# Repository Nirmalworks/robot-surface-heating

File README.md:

# Robotic Surface Heating

A ROS 2 system for autonomous, closed-loop thermal conditioning of a surface. A
Universal Robots UR10e holds a hot-air tool while an array of FLIR thermal
cameras reconstructs a live 3D temperature field. A planning layer continuously
identifies the coldest region of the target surface and directs the arm to heat
it, repeating until the surface reaches a uniform temperature.

---

## Table of contents

1. [Overview](#1-overview)
2. [What this project achieves](#2-what-this-project-achieves)
3. [ROS 2 concepts used here](#3-ros-2-concepts-used-here)
4. [System architecture](#4-system-architecture)
5. [Runtime pipeline](#5-runtime-pipeline)
6. [Controllers compared: Greedy vs. MPC](#6-controllers-compared-greedy-vs-mpc)
7. [Project structure](#project-structure)
8. [Source files by package (detailed reference)](#7-source-files-by-package-detailed-reference)
9. [Configuration](#8-configuration)
10. [Starting a new "move-only" project](#9-starting-a-new-move-only-project)
11. [Driving the arm from a custom model](#10-driving-the-arm-from-a-custom-model)
12. [Quick start  running the heating demo](#11-quick-start--running-the-heating-demo)
13. [Full research paper](#12-research-paper)
14. [TRIAC intensity stage: circuit files](#13-triac-intensity-stage-circuit-files)
15. [Experiment photos and videos](#14-experiment-photos-and-videos)

---

## 1. Overview

The system runs a single control loop. Thermal cameras observe the surface, the
perception layer locates the coldest region, the planner converts that region
into a target pose, and the arm moves there and applies heat. As each cold spot
warms, a new coldest region appears, and the loop continues until the surface is
evenly heated.

---

## 2. What this project achieves

This work automates a process that is normally manual: bringing a surface to a
uniform target temperature with a robot-mounted heat gun. The contribution is
that **both the trajectory and the heating intensity are controlled together** —
prior automated approaches move the tool but leave intensity fixed.

**System built**

- A **TRIAC-based intensity stage** (custom PCB) that modulates the 1500 W heat
  gun via phase-angle firing, giving continuous, repeatable control of delivered
  power. Open-loop characterization is monotonic and repeatable across the firing
  range.
- A **multi-camera FLIR Lepton thermal pipeline** that fuses several thermal
  views into a single live 3D temperature field, with URDF-based occlusion
  masking so the arm itself is removed from the reconstruction.
- A **physics-based thermal model** (2D finite-difference heat diffusion with a
  moving Gaussian source) fit offline in PyTorch and validated against an
  NVIDIA Warp solver. The model lets the planner predict how heat will spread.
- A **closed-loop planning layer** that re-plans continuously and drives the arm
  toward whichever region is coldest or out of band.

**Headline result**

A head-to-head experiment compared three controllers on a planar composite panel
(10 mm analysis grid, 40–50 °C target band, firing clamped to 25–65 %, five
trials per policy). The adaptive controller (**MPC Dynamic**) holds **87–90 % of
the surface inside the target band at steady state, versus ~55 % for the
static baseline** — roughly a 1.6× improvement in uniform coverage.

---

## 3. ROS 2 concepts used here

The software is organized as a set of independent processes called **nodes**.
Nodes do not call each other directly; they exchange data over named channels.

- **Publisher** — a node that writes messages to a topic.
- **Subscriber** — a node that reads messages from a topic.
- **Topic** — a named, typed message channel (for example `/coldest_pose`). Any
  node may publish or subscribe to it.
- **Service** — a request/response call: a node sends a request and blocks until
  it receives a reply.
- **TF tree** — the live coordinate-frame graph describing where every link of
  the robot and every camera sits in space.

---

## 4. System architecture

The stack is layered from the physical hardware down to the software that drives
it. Each layer depends only on the one above it.

---

## 5. Runtime pipeline

The diagram below shows the nodes that run during a live demo and the topics
that connect them.

### Key topics

| Topic | Payload | Publisher | Subscriber |
|---|---|---|---|
| `/thermal_camera_*/image_raw` | Raw thermal images | Camera publisher | Point-cloud coloration |
| `/raw_thermal_pointcloud` | 3D points with temperature | Point-cloud coloration | Brain, surface picker |
| `/colored_cad_pointcloud` | Colored cloud for RViz | Point-cloud coloration | RViz |
| `robot_mask` | Pixels belonging to the arm | `robot_mask_pub` | Point-cloud coloration |
| `/selected_surface_points` | The selected target surface | Surface picker | Brain, data collectors |
| `/coldest_pose`, `/hottest_pose` | Extremum pose + temperature | Brain | Robot interface |
| `/robot_target_pose` | Target pose for the arm | Brain | Robot interface |
| `/joint_states` | Current joint angles | Robot driver | Mask, coloration |

### Custom messages

- **`Extrema`** — header, a list of poses, and a scalar `value` (temperature).
  Used to communicate cold/hot spots.
- **`RobotMask`** — header plus camera images marking where the robot occupies
  the frame.
- **`PoseToPlan`** (service) — accepts a position and orientation, returns
  `success: true/false`.

---

## 6. Controllers compared: Greedy vs. MPC

The planning layer is the part that decides *where to heat next*, and the project
evaluated three strategies. They differ in whether they use a thermal model and
whether they reason about the future.

### The three policies

| Policy | Uses a model? | Plans ahead? | Intensity | File |
|---|---|---|---|---|
| **Greedy** | No | No | Fixed firing % | `greedy_replanner.py` |
| **MPC Static** | Yes | Yes (4 s horizon) | One fixed % per plan | `mpc_test_1.py` / `extrema_pub_modular.py` |
| **MPC Dynamic** | Yes | Yes (4 s horizon) | Varies along the path | `continuous_replanner.py` |

### How Greedy works

Find the coldest cell in the fused grid, point the heat gun at it, fire at a
fixed percentage, repeat. No model, no horizon, no temporal reasoning. Two
failure modes follow directly:

- **Oscillation (spatial pathology).** Once the coldest cell warms, a neighbor
  becomes coldest, so the arm jumps back and forth across a cluster of cold
  cells, never letting any of them stabilize.
- **Overshoot (temporal pathology).** A fixed firing percentage with no temporal
  authority means cells the arm dwells over blow past the target band.

### How MPC works

Re-plan every 2 seconds over a 4-second horizon:

1. Read the fused thermal grid.
2. Sample *K* candidate target cells (cold or out of band).
3. Fit *K* B-spline paths from the current end-effector pose to each target.
4. Roll out every candidate forward 4 s under the learned thermal model
   (batched GPU rollout).
5. Score each with the cost function below.
6. Execute the first 2 s of the winning plan, then re-plan.

The cost function balances getting on-temperature against smooth, short paths:

```
J = J_temp + λ_c · J_curv + λ_l · J_len
```

**MPC Static** uses one fixed firing percentage per plan. **MPC Dynamic** lets
the firing percentage vary along the trajectory, which is what gives it temporal
authority over each cell.

### Results

| Policy | Time to band | Steady-state in-band coverage |
|---|---|---|
| Greedy | — (overshoots, never stabilizes) | low / unstable |
| MPC Static | **58.6 s** (SD 5.1 s) | ~55 % |
| MPC Dynamic | 85.8 s (SD 7.3 s) | **87–90 %** |

The apparent paradox is the point: **MPC Static reaches the band *faster*, but
MPC Dynamic *stays* in band**. Time-to-band is only half the story — Static
enters quickly but then drifts out (temporal pathology), while Dynamic, by
varying intensity along the path, solves both the oscillation (spatial) and the
drift (temporal) problems. Jointly optimizing trajectory *and* intensity is what
delivers uniform coverage.

---

## Project structure

A map of every Python file, grouped by package. Legend: **● live · ○ experimental / legacy · ◆ shared helper.**

```text
robot_surface_heating/
└── src/
    ├── thermal_camera/                    # sensing, perception, planning (core)
    │   ├── config/
    │   │   ├── camera_params.yaml
    │   │   ├── pnp_calibration_config.yaml
    │   │   ├── cad_register_config.yaml
    │   │   └── pcl_params.yaml
    │   └── thermal_camera/
    │       │  # --- camera acquisition ---
    │       ├── ● publisher_thermal.py             # reads FLIR cameras, publishes thermal images
    │       ├── ◆ uvctypes.py                      # libuvc Python bindings
    │       ├── ● uvc_visualize.py                 # live 2D thermal viewer (per camera)
    │       ├── ○ uvc-radiometry_2.py              # older single-camera viewer
    │       ├── ○ realsense_calib_test.py          # RealSense depth test (off main path)
    │       │  # --- calibration & frames ---
    │       ├── ● camera_frame_broadcaster.py      # publishes camera poses to TF
    │       ├── ● pnp_extrinsic.py                 # extrinsic calibration (click correspondences)
    │       ├── ○ extrinsic.py                     # alternate extrinsic calibration
    │       ├── ○ thermal-intrinsic-calibration.py # per-camera intrinsic calibration
    │       ├── ● bundle_adjustment.py             # joint refinement of all camera poses
    │       ├── ◆ transform_formatting.py          # transform formatting helper
    │       │  # --- 3D thermal reconstruction ---
    │       ├── ● pointcloud_coloration.py         # projects thermal pixels to 3D (multi-cam)
    │       ├── ○ pointcloud_coloration_single.py  # single-camera variant
    │       ├── ○ thermal_pointcloud.py            # early prototype
    │       ├── ● robot_mask_pub.py                # masks arm pixels from coloration
    │       ├── ● virtual_camera_viewer.py         # virtual arm view from joint angles
    │       ├── ○ mask_playback.py                 # replays saved masks
    │       ├── ● realtime_masked_visualizer.py    # live masked thermal grid
    │       │  # --- CAD model ---
    │       ├── ● cad_visualization.py             # loads CAD/STL, displays in RViz
    │       ├── ◆ cad_registration.py              # registers CAD to live cloud
    │       ├── ● stl_to_lattice.py                # STL surface -> targetable point grid
    │       ├── ○ stl_to_lattice_old1.py           # older version
    │       ├── ○ txt_to_lattice.py                # lattice from text dump (experimental)
    │       ├── ○ txt_processing.py                # text model processing (experimental)
    │       │  # --- planning: extremum detection & policies ---
    │       ├── ● extrema_pub.py                    # primary planner -> /robot_target_pose
    │       ├── ● extrema_pub_modular.py           # configurable planner + coverage metric
    │       ├── ○ extrema_pub_curobo.py            # cuRobo GPU-planner variant
    │       ├── ○ coldest_pose_pub.py              # older standalone coldest-spot publisher
    │       ├── ● hottest_temp_pub.py              # publishes hottest temperature value
    │       ├── ● greedy_replanner.py              # greedy policy (nearest cold spot)
    │       ├── ● continuous_replanner.py          # adaptive re-planning policy
    │       ├── ○ continuous_replanner_old*.py     # 6 legacy versions
    │       ├── ● zigzag_policy.py                 # zig-zag sweep policy
    │       ├── ● optimize_single_real.py          # single-step optimizer (learned model)
    │       ├── ○ optimize_single_real_old6.py     # older version
    │       ├── ● mpc_test_1.py                    # model-predictive-control experiment
    │       ├── ◆ single_horizon.py                # single-step math for MPC/optimizer
    │       ├── ◆ adhesive_single.py               # material/heat-transfer helper
    │       ├── ◆ learned_model_util.py            # loads learned thermal model
    │       ├── ● thermal_model_reader.py          # trains/uses the thermal model
    │       │  # --- surface selection & paths ---
    │       ├── ● o3d_visual_surface.py            # interactive surface picker
    │       ├── ○ o3d_visual_surface_old1.py       # older picker
    │       ├── ○ o3d_visual_surface_old2.py       # older picker
    │       ├── ● heater_path_to_cartesian.py      # heating path -> 3D waypoints
    │       ├── ● heating_path_data_collection.py  # builds/serves heating path (services)
    │       ├── ◆ common_motionplan_utilities.py   # shared motion math (normals, offsets)
    │       ├── ● debug_surface_normals.py         # surface-normal debug overlay
    │       │  # --- heat-gun control ---
    │       ├── ● heat_gun_controller.py           # sets heat-gun power via Arduino (serial)
    │       ├── ● heater_manual.py                 # manual terminal heat-gun control
    │       ├── ○ arduino_dummy.py                 # mock Arduino for testing
    │       │  # --- recording & replay ---
    │       ├── ● thermal_data_collector.py        # records cloud + poses to rosbag
    │       ├── ● rosbag_reader.py                 # rosbag -> .npz dataset
    │       ├── ○ traj_rosbag_reader.py            # rosbag -> dataset + trajectories
    │       ├── ● thermal_rerun.py                 # streams recorded data to Rerun viewer
    │       ├── ● live_temp_plotter.py             # live surface-temperature plot
    │       ├── ○ temp_data_analysis.py            # one-off .npz plotting
    │       ├── ○ timestamp_comparator.py          # checks camera timestamp alignment
    │       ├── ◆ read_write_pkl.py                # pickle read/write helper
    │       └── ○ pyrender_urdf_test.py            # URDF rendering test
    │
    ├── robot_interface/                    # arm execution
    │   └── robot_interface/
    │       ├── ● overheat_safety_robot_interface.py # primary executor (MoveIt + safety)
    │       ├── ● demo_robot_interface.py          # executor for the RSS demo
    │       ├── ● modular_executor.py              # configurable executor (debug topics)
    │       ├── ● dual_robot_interface.py          # controls two arms
    │       ├── ● heater_path_executor.py          # executes a full heating path
    │       ├── ● lightweight_executor.py          # minimal executor — START HERE for custom nodes
    │       ├── ● lightweight_executor_heat_gun.py # minimal executor + heat gun
    │       ├── ○ lightweight_executor_old.py      # older version
    │       ├── ◆ moveit_waitable.py               # awaits MoveIt async results
    │       ├── ◆ curobo_planner.py                # optional cuRobo (GPU) planner wrapper
    │       ├── ○ moveit_test.py                   # MoveIt Cartesian-planning demo
    │       ├── ● live_temp_plotter.py             # live temperature plot
    │       ├── ○ async_node.py                    # minimal example node
    │       ├── ○ execute.py                       # example PoseToPlan client
    │       ├── ○ dump.py                          # scratch/dev interface
    │       ├── ○ gripper_test_node.py             # gripper test
    │       ├── ○ test_robot_interface.py          # test executor
    │       ├── ○ test_robot_interface_new.py      # test executor
    │       ├── ○ rin_boilerplate_code.py          # starter template
    │       └── ○ toy_executor_stub.py             # mock executor (no real robot)
    │
    ├── thermal_camera_interfaces/          # message definitions only
    │   └── msg/
    │       ├── Extrema.msg
    │       └── RobotMask.msg
    │
    ├── lerobot_interface/                  # optional LeRobot bridge
    │   └── lerobot_interface/
    │       └── ○ robot_control_node.py            # bridge to a LeRobot-style arm
    │
    ├── fake_gripper_publisher/             # simulated gripper
    │   └── fake_gripper_publisher/
    │       └── ○ fake_joint_state_publisher.py    # fake gripper joint states for sim
    │
    └── (vendored, off-the-shelf — mostly launch/setup files)
        ├── ur_robot_driver/                       # UR ROS 2 driver
        ├── Universal_Robots_ROS2_Description/     # robot URDF + meshes
        └── thermal_moveit_config/                 # MoveIt config for this cell
```

## 7. Source files by package (detailed reference)

Legend: **● live system · ○ experimental / legacy (safe to ignore while
learning) · ◆ shared helper imported by other files.**

### `thermal_camera` — sensing, perception, and planning (core)

**Camera acquisition**

| File | Description |
|---|---|
| ● `publisher_thermal.py` | Reads the FLIR thermal cameras and publishes thermal images. |
| ◆ `uvctypes.py` | Python bindings to the camera USB library (`libuvc`). |
| ● `uvc_visualize.py` | Live 2D thermal viewer windows, one per camera. |
| ○ `uvc-radiometry_2.py` | Older single-camera viewer experiment. |
| ○ `realsense_calib_test.py` | RealSense depth-camera test (not on the main path). |

**Camera calibration and frames**

| File | Description |
|---|---|
| ● `camera_frame_broadcaster.py` | Publishes each camera's pose to TF. |
| ● `pnp_extrinsic.py` | Extrinsic calibration: click corresponding points to recover each camera's pose. |
| ○ `extrinsic.py` | Alternate/older extrinsic calibration. |
| ○ `thermal-intrinsic-calibration.py` | Per-camera intrinsic (lens) calibration. |
| ● `bundle_adjustment.py` | Joint refinement of all camera poses for higher accuracy. |
| ◆ `transform_formatting.py` | Transform formatting/cleanup helper. |

**3D thermal reconstruction**

| File | Description |
|---|---|
| ● `pointcloud_coloration.py` | Projects thermal pixels onto 3D points (multi-camera). |
| ○ `pointcloud_coloration_single.py` | Single-camera variant. |
| ○ `thermal_pointcloud.py` | Early prototype of the thermal cloud. |
| ● `robot_mask_pub.py` | Identifies arm pixels so they are excluded from coloration. |
| ● `virtual_camera_viewer.py` | Renders a virtual camera view of the arm from joint angles (used for masking). |
| ○ `mask_playback.py` | Replays saved masks for testing. |
| ● `realtime_masked_visualizer.py` | Live view of the masked thermal grid. |

**CAD model**

| File | Description |
|---|---|
| ● `cad_visualization.py` | Loads the part's CAD/STL model and displays it in RViz. STL path is set here. |
| ◆ `cad_registration.py` | Registers the CAD model against the live point cloud. |
| ● `stl_to_lattice.py` | Converts an STL surface into a grid of targetable points. |
| ○ `stl_to_lattice_old1.py` | Older version of the above. |
| ○ `txt_to_lattice.py` / `txt_processing.py` | Build/process lattices from text model dumps (experimental). |

**Planning — extremum detection and policies**

| File | Description |
|---|---|
| ● `extrema_pub.py` | Primary planner: locates the coldest and hottest spots, publishes `/robot_target_pose`. |
| ● `extrema_pub_modular.py` | Configurable planner that also publishes greedy targets and in-band coverage. |
| ○ `extrema_pub_curobo.py` | Planner variant using the cuRobo GPU planner. |
| ○ `coldest_pose_pub.py` | Older standalone coldest-spot publisher. |
| ● `hottest_temp_pub.py` | Publishes the single hottest temperature value. |
| ● `greedy_replanner.py` | Greedy policy: always heat the nearest cold spot next. |
| ● `continuous_replanner.py` | Adaptive policy: re-plans the path as the surface heats. |
| ○ `continuous_replanner_old*.py` | Six legacy versions of the continuous policy. |
| ● `zigzag_policy.py` | Sweeps the tool over the surface in a zig-zag pattern. |
| ● `optimize_single_real.py` | Optimizes a single heating step using a learned thermal model. |
| ○ `optimize_single_real_old6.py` | Older version of the above. |
| ● `mpc_test_1.py` | Model-predictive-control heating experiment. |
| ◆ `single_horizon.py` | Single-step math helper for the MPC/optimizer. |
| ◆ `adhesive_single.py` | Material/heat-transfer helper for the planners. |
| ◆ `learned_model_util.py` | Loads the learned thermal (heat-diffusion) model. |
| ● `thermal_model_reader.py` | Reads recorded data and trains/uses the thermal model. |

**Surface selection and paths**

| File | Description |
|---|---|
| ● `o3d_visual_surface.py` | Interactive picker for selecting the surface to heat. |
| ○ `o3d_visual_surface_old1.py` / `_old2.py` | Older versions of the picker. |
| ● `heater_path_to_cartesian.py` | Converts a heating path into 3D robot waypoints. |
| ● `heating_path_data_collection.py` | Builds/serves a heating path; offers `/select_heating_path` and `/publish_heating_path` services. |
| ◆ `common_motionplan_utilities.py` | Shared motion math (e.g. tool offset along surface normals). |
| ● `debug_surface_normals.py` | Debug overlay of surface-normal arrows. |

**Heat-gun control**

| File | Description |
|---|---|
| ● `heat_gun_controller.py` | Sets heat-gun power via the Arduino over serial, based on heat metrics. |
| ● `heater_manual.py` | Manual terminal control of the heat gun. |
| ○ `arduino_dummy.py` | Mock Arduino for hardware-free testing. |

**Data recording and replay**

| File | Description |
|---|---|
| ● `thermal_data_collector.py` | Records the live cloud and robot poses to a rosbag. |
| ● `rosbag_reader.py` | Reads a rosbag and exports it as an `.npz` dataset. |
| ○ `traj_rosbag_reader.py` | As above, also saving trajectory/joint data. |
| ● `thermal_rerun.py` | Streams recorded data into the Rerun 3D viewer. |
| ● `live_temp_plotter.py` | Live temperature plot for the selected surface. |
| ○ `temp_data_analysis.py` | One-off `.npz` plotting script. |
| ○ `timestamp_comparator.py` | Checks camera timestamp alignment. |
| ◆ `read_write_pkl.py` | Small pickle read/write helper for debugging. |
| ○ `pyrender_urdf_test.py` | URDF rendering test with pyrender. |

### `robot_interface` — arm execution

| File | Description |
|---|---|
| ● `overheat_safety_robot_interface.py` | Primary executor: subscribes to `/robot_target_pose`, plans with MoveIt, moves the arm with safety checks. |
| ● `demo_robot_interface.py` | Executor used in the full RSS demo. |
| ● `modular_executor.py` | Configurable executor wired to debug topics and the heating path. |
| ● `dual_robot_interface.py` | Controls two arms simultaneously. |
| ● `heater_path_executor.py` | Executes a full heating path with the heat gun. |
| ● `lightweight_executor.py` | Minimal, fast executor. **Best reference when writing a custom move node.** |
| ● `lightweight_executor_heat_gun.py` | Minimal executor that also toggles the heat gun. |
| ○ `lightweight_executor_old.py` | Older version. |
| ◆ `moveit_waitable.py` | Helper for awaiting MoveIt async results. |
| ◆ `curobo_planner.py` | Optional cuRobo (GPU) motion-planner wrapper. |
| ○ `moveit_test.py` | MoveIt Cartesian-planning demo. |
| ● `live_temp_plotter.py` | Live temperature plot, runnable from this package. |
| ○ `async_node.py` | Minimal example node subscribing to `debug_cold_pose`. |
| ○ `execute.py` | Example client for the `PoseToPlan` service. |
| ○ `dump.py` | Scratch/dev version of the robot interface. |
| ○ `gripper_test_node.py` | Gripper test. |
| ○ `test_robot_interface.py` / `_new.py` | Test executors that publish `/robot_target_pose`. |
| ○ `rin_boilerplate_code.py` | Starter template. |
| ○ `toy_executor_stub.py` | Mock executor (no real robot). |

### `thermal_camera_interfaces` — message definitions

Message definitions only (`Extrema.msg`, `RobotMask.msg`). No runtime logic;
`__init__.py` is empty.

### `lerobot_interface` — optional LeRobot bridge

| File | Description |
|---|---|
| ○ `robot_control_node.py` | Bridge to a LeRobot-style arm. Optional, not part of the heating demo. |
| | `test_copyright/flake8/pep257.py` are auto-generated lint tests. |

### `fake_gripper_publisher` — simulated gripper

| File | Description |
|---|---|
| ○ `fake_joint_state_publisher.py` | Publishes fake gripper joint states so the robot model is complete in simulation. |

### Vendored packages

`ur_robot_driver`, `Universal_Robots_ROS2_Description`, and
`thermal_moveit_config` are standard, off-the-shelf Universal Robots / MoveIt
packages. Their Python files are mostly launch and setup scripts that start the
driver, load the robot URDF, and configure MoveIt. **Do not remove the
description package** — the arm requires it to know its own geometry.

---

## 8. Configuration

Most behavior is configurable without code changes. In
`src/thermal_camera/config/`:

| File | Settings |
|---|---|
| `camera_params.yaml` | `camera_count` and `extrinsics_prefix` (which calibration to load). |
| `pnp_calibration_config.yaml` | `camera_count` and the output path for new calibrations. |
| `cad_register_config.yaml` | CAD registration settings. |
| `pcl_params.yaml` | Point-cloud filtering settings. |

In `cad_visualization.py`, the line `STL_FILE_PATH = ".../RSS_v3.stl"` selects
which part's CAD model is loaded.

---

## 9. Starting a new "move-only" project

To build a clean project that only moves the UR arm — without any thermal or
heating code — keep the robot-driving foundation and remove the rest. Motion
control itself is provided off the shelf by the Universal Robots ROS 2 driver
and MoveIt; you do not write a driver. The heating code sits entirely on top of
that foundation.

### Keep — the robot-driving foundation

| Package | Role | Why keep |
|---|---|---|
| `ur_robot_driver` | Connects ROS to the UR10e and exposes its controllers. | This is the driver. |
| `Universal_Robots_ROS2_Description` | Robot URDF and meshes (geometry, joints, limits). | The arm needs its own model. |
| `thermal_moveit_config` *(optional, rename)* | MoveIt config for this cell. | Keep for ready-made motion planning; rename to drop "thermal". |

### Drop — heating-specific packages

`thermal_camera`, `thermal_camera_interfaces`, `lerobot_interface`,
`fake_gripper_publisher`, **and `robot_interface`**.

> **Do not reuse `robot_interface` as-is.** Its executors (e.g.
> `overheat_safety_robot_interface.py`) import `thermal_camera_interfaces` and
> `common_motionplan_utilities`, so they will not build once the thermal
> packages are removed. Use them only as a reference for how to call MoveIt, then
> write a clean node of your own.

### Recommended workspace layout

```
my_new_robot_ws/
└── src/
    ├── ur_robot_driver/                       # the driver
    ├── Universal_Robots_ROS2_Description/     # robot body (URDF/meshes)
    ├── thermal_moveit_config/  (renamed)      # motion planning (optional)
    └── my_robot_task/                         # your new code
        ├── package.xml
        ├── setup.py
        └── my_robot_task/
            └── move_node.py                   # decides where to move
```

### Moving the arm in three steps

**1. Bring up the robot:**

```bash
ros2 launch ur_robot_driver ur10e.launch.py robot_ip:=<ROBOT_IP>
ros2 launch ur_moveit_config ur_moveit.launch.py        # only if you want planning
```

**2. Send goals from `move_node.py`.** Choose one of two styles:

- **Direct (no planning):** publish a `JointTrajectory` to
  `/scaled_joint_trajectory_controller/joint_trajectory` (or use the
  `FollowJointTrajectory` action) to drive the joints to chosen angles. Simplest
  starting point.
- **Collision-aware:** call MoveIt's `GetCartesianPath` service or the
  `MoveGroup` action with a target **pose**, then execute the returned
  trajectory. `lightweight_executor.py` demonstrates this MoveIt call pattern —
  reuse the structure but remove the `thermal_camera_interfaces` / `Extrema`
  imports.

**3. Build and run:**

```bash
colcon build --symlink-install
source install/setup.bash
ros2 run my_robot_task move_node
```

### Using a different arm

Replace `ur_robot_driver` and `Universal_Robots_ROS2_Description` with your
robot's ROS 2 driver and description package, and use that vendor's MoveIt
config. The `move_node.py` pattern is unchanged; only the controller and topic
names differ.

---

## 10. Driving the arm from a custom model

Any decision-maker can drive the arm — the heating planner is just one option.
A vision model, a reinforcement-learning policy, or a plain script can all
produce goals; the arm is agnostic to their source.

The model outputs a target (a pose or a set of joint angles). `move_node.py`
receives it, hands it to MoveIt and the driver, and the arm executes a safe
path. That is the entire integration.

---

## 11. Quick start — running the heating demo

Run each command in its own terminal from `robot_surface_heating/`, after
`source install/setup.bash`:

```bash
ros2 launch ur_robot_driver thermal_ur_control.launch.py    # 1. robot driver
ros2 launch thermal_moveit_config thermal_moveit.launch.py  # 2. MoveIt
ros2 launch thermal_camera cams_and_cad.launch.py           # 3. cameras + CAD
ros2 launch thermal_camera pcl_analysis.launch.py           # 4. surface selection
ros2 launch thermal_camera policy_launch.launch.py          # 5. planning policy
ros2 run robot_interface overheat_safety_robot_interface.py # 6. arm execution
```

In RViz, add a **PointCloud2** display on `/selected_surface_points` and set its
reliability to *Best Effort*.

---

## 12. Research paper

This project is written up as a paper. The source PDF is checked into the repo
at [`paper/Adaptive_Robotic_Surface_Heating.pdf`](paper/Adaptive_Robotic_Surface_Heating.pdf)

### Summary

- **Heating demo:** cameras observe heat → a 3D thermal cloud is built → the
  planner locates the coldest spot → the arm moves there → the heat gun warms it
  → repeat.
- **Move-only project:** keep `ur_robot_driver`, the UR description, and a MoveIt
  config; drop everything `thermal_*` and `robot_interface`; and write one small
  `move_node.py` that sends a joint or pose goal from any source, including a
  custom model.

---

## 13. TRIAC intensity stage: circuit files

The custom PCB referenced in [section 2](#2-what-this-project-achieves) that
modulates the 1500 W heat gun via phase-angle firing is checked into the repo
root:

- [`Circuit .kicad_pcb`](Circuit%20.kicad_pcb) — KiCad PCB layout for the
  TRIAC-based intensity stage.
- [`Print Schematic.pdf`](Print%20Schematic.pdf) — printable schematic of the
  same circuit.

---

## 14. Experiment photos and videos

Raw photos and clips from five physical test parts are checked into
[`media/experiments/`](media/experiments/): **black composite**, **honeycomb**,
**metal bumper**, **saddle mold**, and **shell mold**. For each part the set
generally includes:

- **Setup photos** — the part mounted in the test cell.
- **End-effector photos** — the heat-gun tool head (pointed nozzle, light-bulb,
  and heat-gun variants) in position over the part.
- **Selection views** (`local` / `large` / `contour`) — the surface region
  picked in the `o3d_visual_surface.py` picker.
- **RViz views** (`local` / `large` / `contour`) — the corresponding live
  thermal point cloud in RViz.
- **Pointcloud / lattice renders** — the reconstructed 3D temperature field and
  its targetable point lattice, some rendered in Matplotlib.

Three short clips are also included: `Video of Black composite part.mp4`,
`Video of Honeycomb Part.mp4`, `video of shell mold (new part).mp4`, and
`RVIZ video of saddle mold.mp4`.

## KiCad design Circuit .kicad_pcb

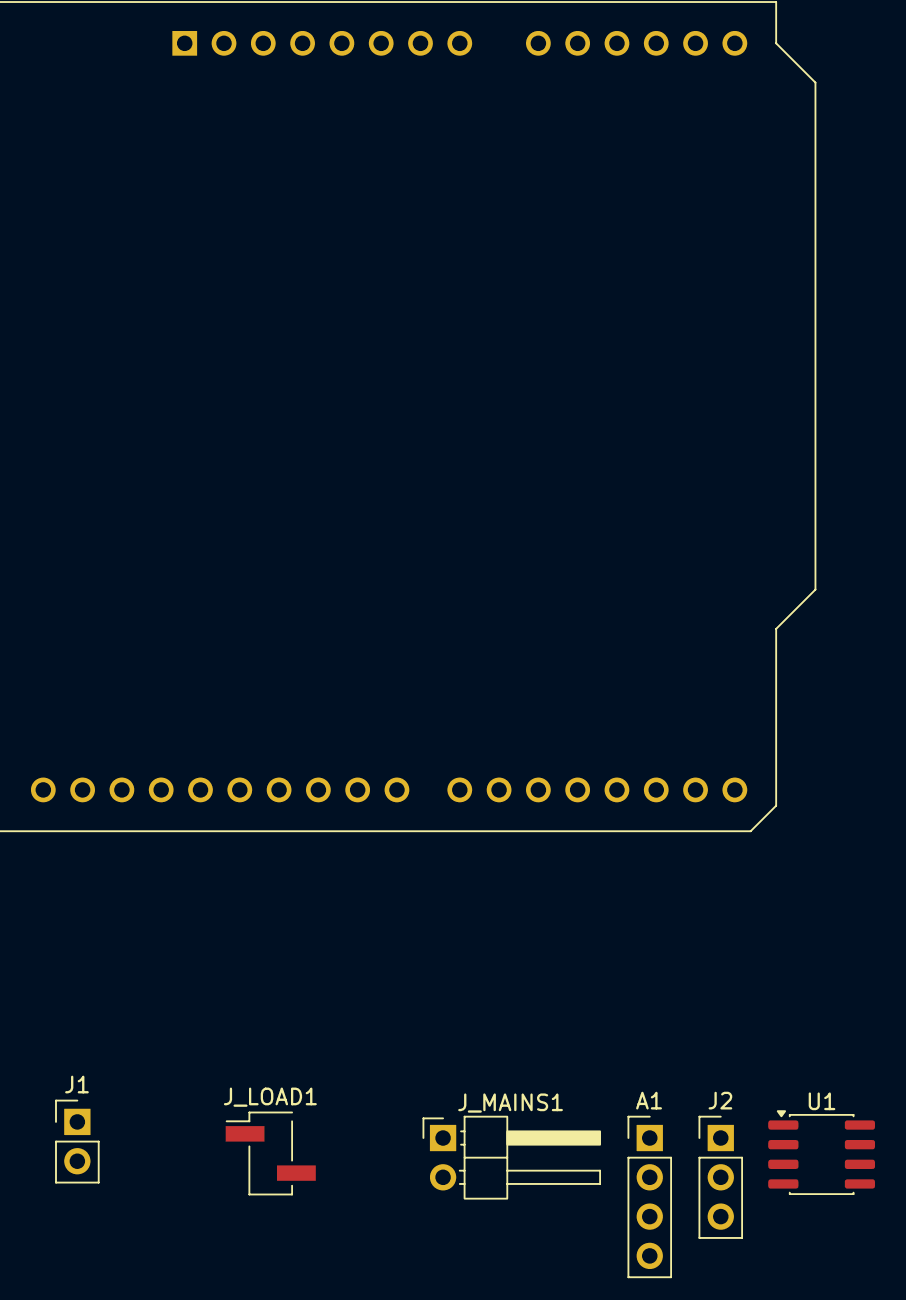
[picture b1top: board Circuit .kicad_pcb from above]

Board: 2 copper layers, 7 parts (0 on the bottom side), 3 nets, no tracks yet.

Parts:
A1: AC_DIMMER; PinHeader_1x04_P2.54mm_Vertical
A2: Arduino_UNO_R3
J1: THERMOCOUPLE_J; PinHeader_1x02_P2.54mm_Vertical
J2: J_DIMMER_AC; PinHeader_1x03_P2.54mm_Vertical
J_LOAD1: Conn_01x02; PinHeader_1x02_P2.54mm_Vertical_SMD_Pin1Left
J_MAINS1: Conn_01x02; PinHeader_1x02_P2.54mm_Horizontal
U1: MAX6675; SOIC-8_3.9x4.9mm_P1.27mm

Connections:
unnamed: A2.25 (D10), U1.6 (CS)
unnamed: A2.27 (D12), U1.5 (SO)
unnamed: A2.28 (D13), U1.7 (SCK)

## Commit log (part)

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2026-06-27 Initial commit: robot surface heating project (UR10e + FLIR thermal)
2026-06-27 Revise README for project clarity and structure
    Updated README to reflect project scope and structure changes, including a new overview, table of contents, and detailed sections on system architecture, runtime pipeline, and configuration.
2026-06-27 Fix image path in README.md
2026-06-27 Fix image paths in README.md
    Updated image paths in README to use relative paths.
2026-06-27 Revise README structure and add project achievements
    Updated the README to reflect project achievements and restructured sections.
2026-06-27 Add newline at end of README.md
    Fix formatting issue by adding a newline at the end of the file.
2026-06-27 Fix formatting in Quick start section of README
